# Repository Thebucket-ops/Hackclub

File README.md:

# BUCKPAD

hackpad for hackclub blueprint
The buckpad is a 11 key macropad with a rotary encoder and a OLED display, and uses QMK firmware.
The case is designed around the colors of gyspy danger from Pacific Rim, as it is one of the greatest films ever with NO sequel.
It mainly serves as a macropad for everyday activity (listening to music, writing etc.)

Features:
-11 keys
-1 EC11 rotary encoder
-1 Oled display

## PCB
here is the PCB (first time ever i do one!), the silkscreen is imported from a Figma image.

PCB design (I added a filling so its a bit messy, yikes)

Schematic for the hackpad

## Case Design
This was my first time working with Fusion and, not gonna lie, i had a ton of fun designing this case

## Firmware
This hackapd uses QMK firmware:
* the rotary encoder changes volume. press to mute
* the other 11 keys currently act as macros (thought i plan on implementing VIA to dynamically change them)
* I plan to set the oled as an audio visualizer once i get my hands on it.

## BOM

* 1x unsoldered Seeed XIAO RP2040
* 1x 0.91 inch OLED display
* 12x through-hole 1N4148 Diodes
* 11 MX-Style switches
* 1x EC11 Rotary encoder
* 11x white blank DSA keycaps
* 4x M3x16mm screws
* 4x M3x5mx4mm heatset inserts
* 1x Case (2 printed parts)

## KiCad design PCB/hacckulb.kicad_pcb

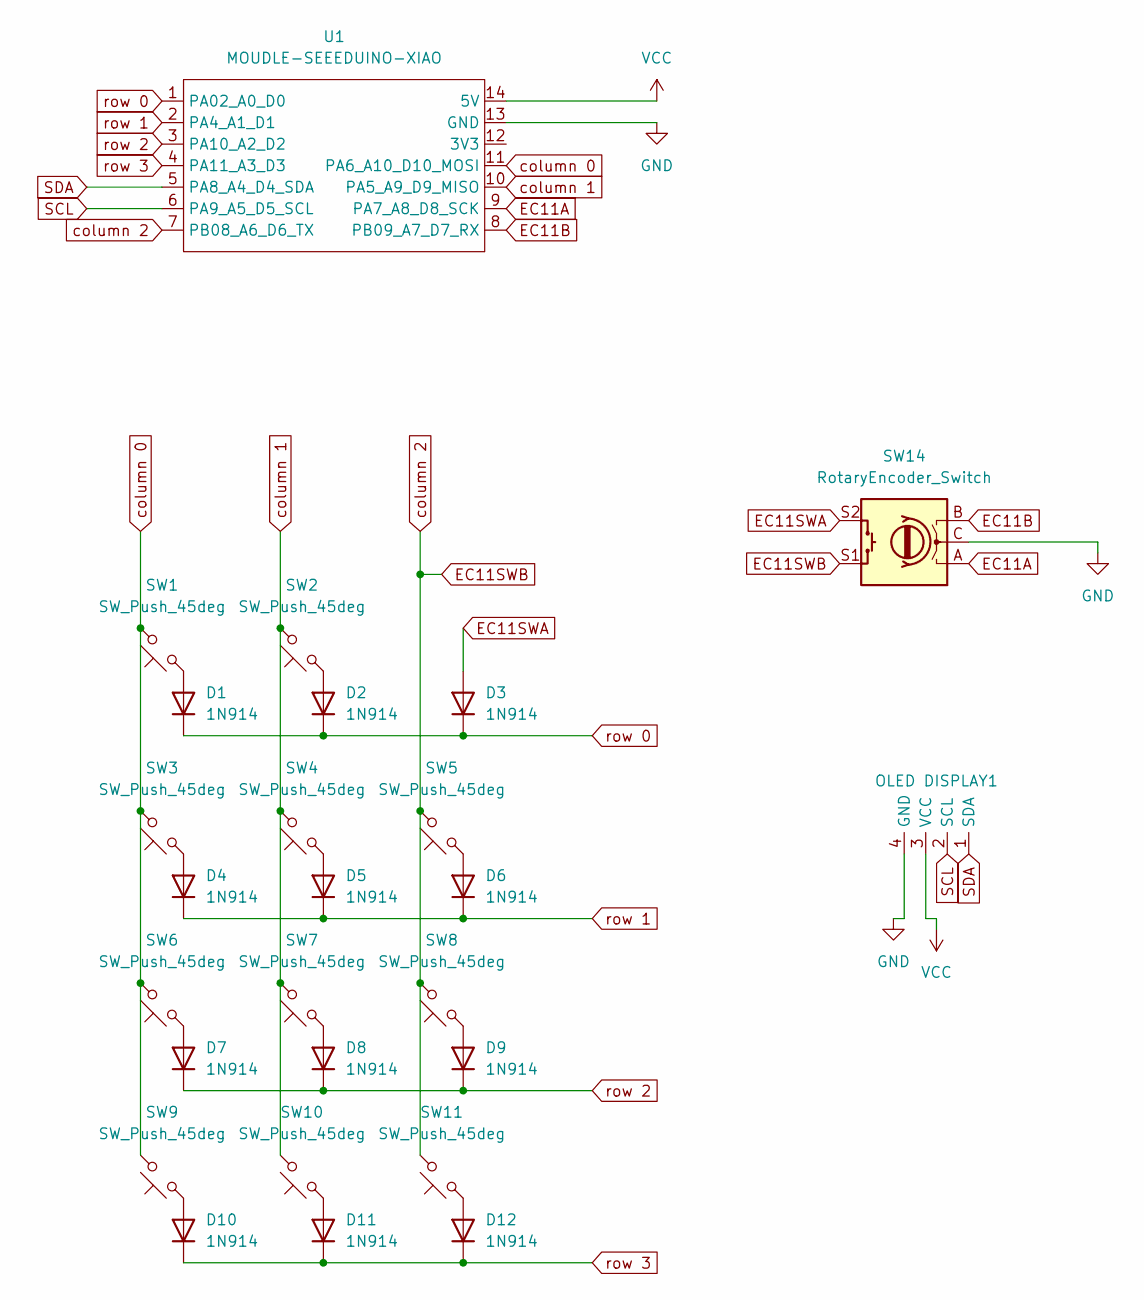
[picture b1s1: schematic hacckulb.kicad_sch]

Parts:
D1, D2, D3, D4, D5, D6, D7, D8, D9, D10, D11, D12: 1N914; D_DO-35_SOD27_P7.62mm_Horizontal
OLED DISPLAY1: SSD1306-0.91-OLED-4pin-128x32
SW1, SW2, SW3, SW4, SW5, SW6, SW7, SW8, SW9, SW10, SW11: SW_Push_45deg; SW_Cherry_MX_1.00u_PCB
SW14: RotaryEncoder_Switch; RotaryEncoder_Alps_EC11E-Switch_Vertical_H20mm
U1: MOUDLE-SEEEDUINO-XIAO; XIAO-Generic-Hybrid-14P-2.54-21X17.8MM

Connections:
EC11A: SW14.A, U1.9 (PA7_A8_D8_SCK)
EC11B: SW14.B, U1.8 (PB09_A7_D7_RX)
EC11SWA: D3.2 (A), SW14.S2
EC11SWB: SW5.2, SW8.2, SW11.2, SW14.S1, U1.7 (PB08_A6_D6_TX)
GND: OLED DISPLAY1.4 (GND), SW14.C, U1.13 (GND)
unnamed: D1.2 (A), SW1.1
unnamed: D2.2 (A), SW2.1
unnamed: D4.2 (A), SW3.1
unnamed: D5.2 (A), SW4.1
unnamed: D6.2 (A), SW5.1
unnamed: D7.2 (A), SW6.1
unnamed: D8.2 (A), SW7.1
unnamed: D9.2 (A), SW8.1
unnamed: D10.2 (A), SW9.1
unnamed: D11.2 (A), SW10.1
unnamed: D12.2 (A), SW11.1
SCL: OLED DISPLAY1.2 (SCL), U1.6 (PA9_A5_D5_SCL)
SDA: OLED DISPLAY1.1 (SDA), U1.5 (PA8_A4_D4_SDA)
VCC: OLED DISPLAY1.3 (VCC), U1.14 (5V)
column 0: SW1.2, SW3.2, SW6.2, SW9.2, U1.11 (PA6_A10_D10_MOSI)
column 1: SW2.2, SW4.2, SW7.2, SW10.2, U1.10 (PA5_A9_D9_MISO)
row 0: D1.1 (K), D2.1 (K), D3.1 (K), U1.1 (PA02_A0_D0)
row 1: D4.1 (K), D5.1 (K), D6.1 (K), U1.2 (PA4_A1_D1)
row 2: D7.1 (K), D8.1 (K), D9.1 (K), U1.3 (PA10_A2_D2)
row 3: D10.1 (K), D11.1 (K), D12.1 (K), U1.4 (PA11_A3_D3)

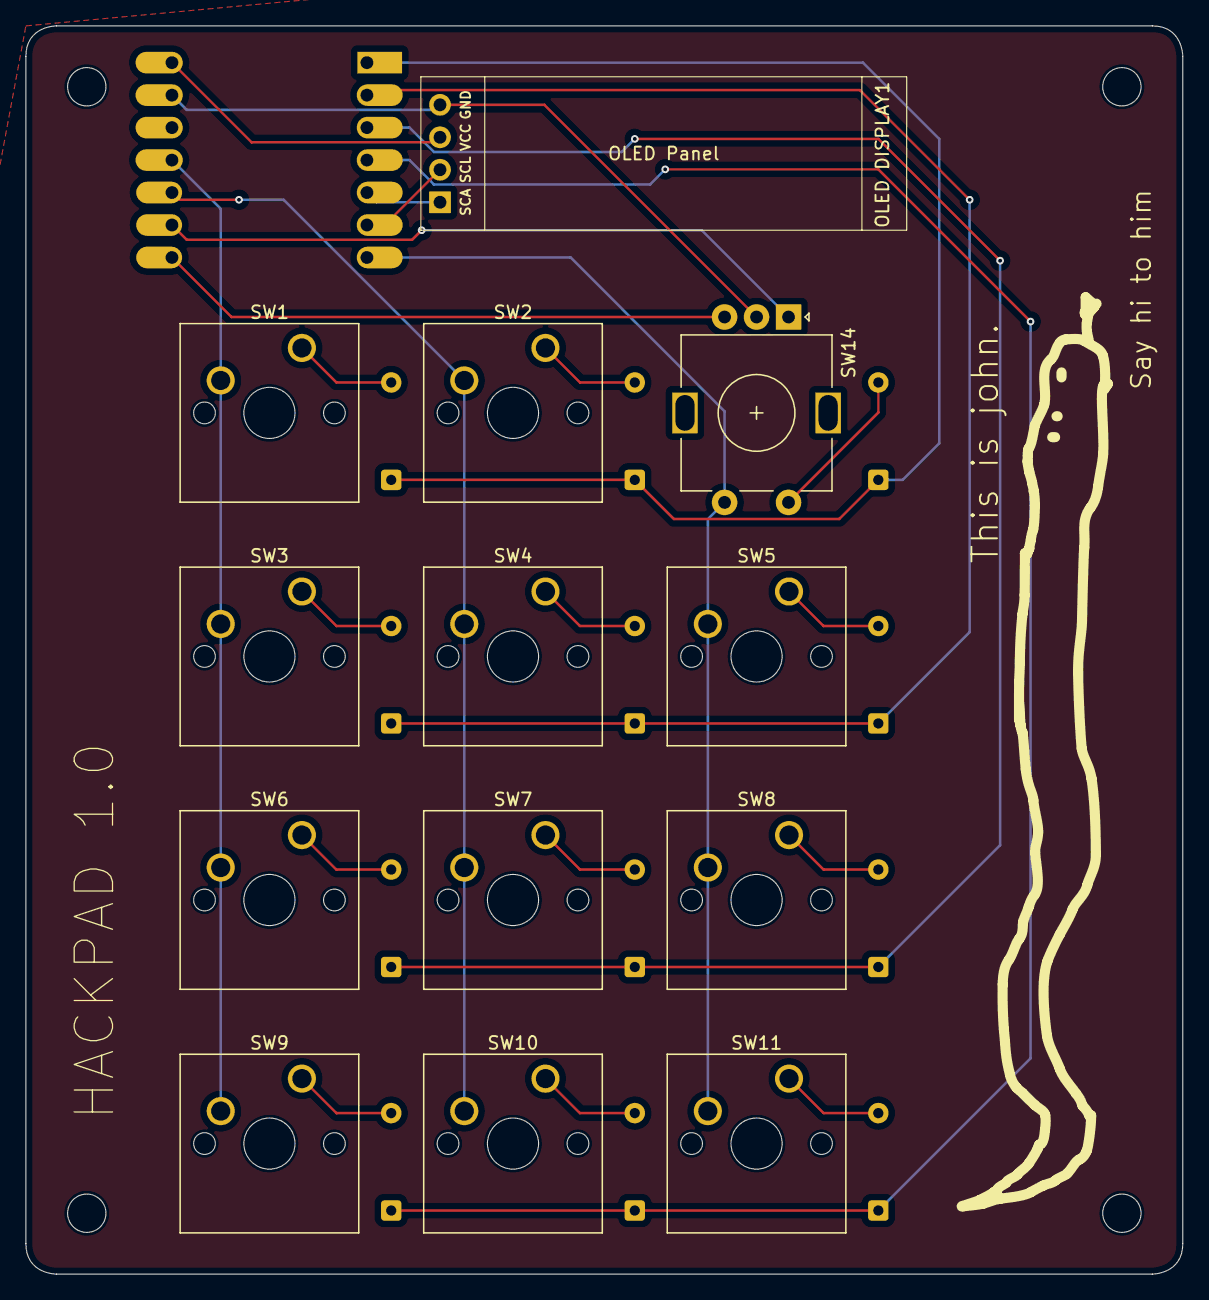
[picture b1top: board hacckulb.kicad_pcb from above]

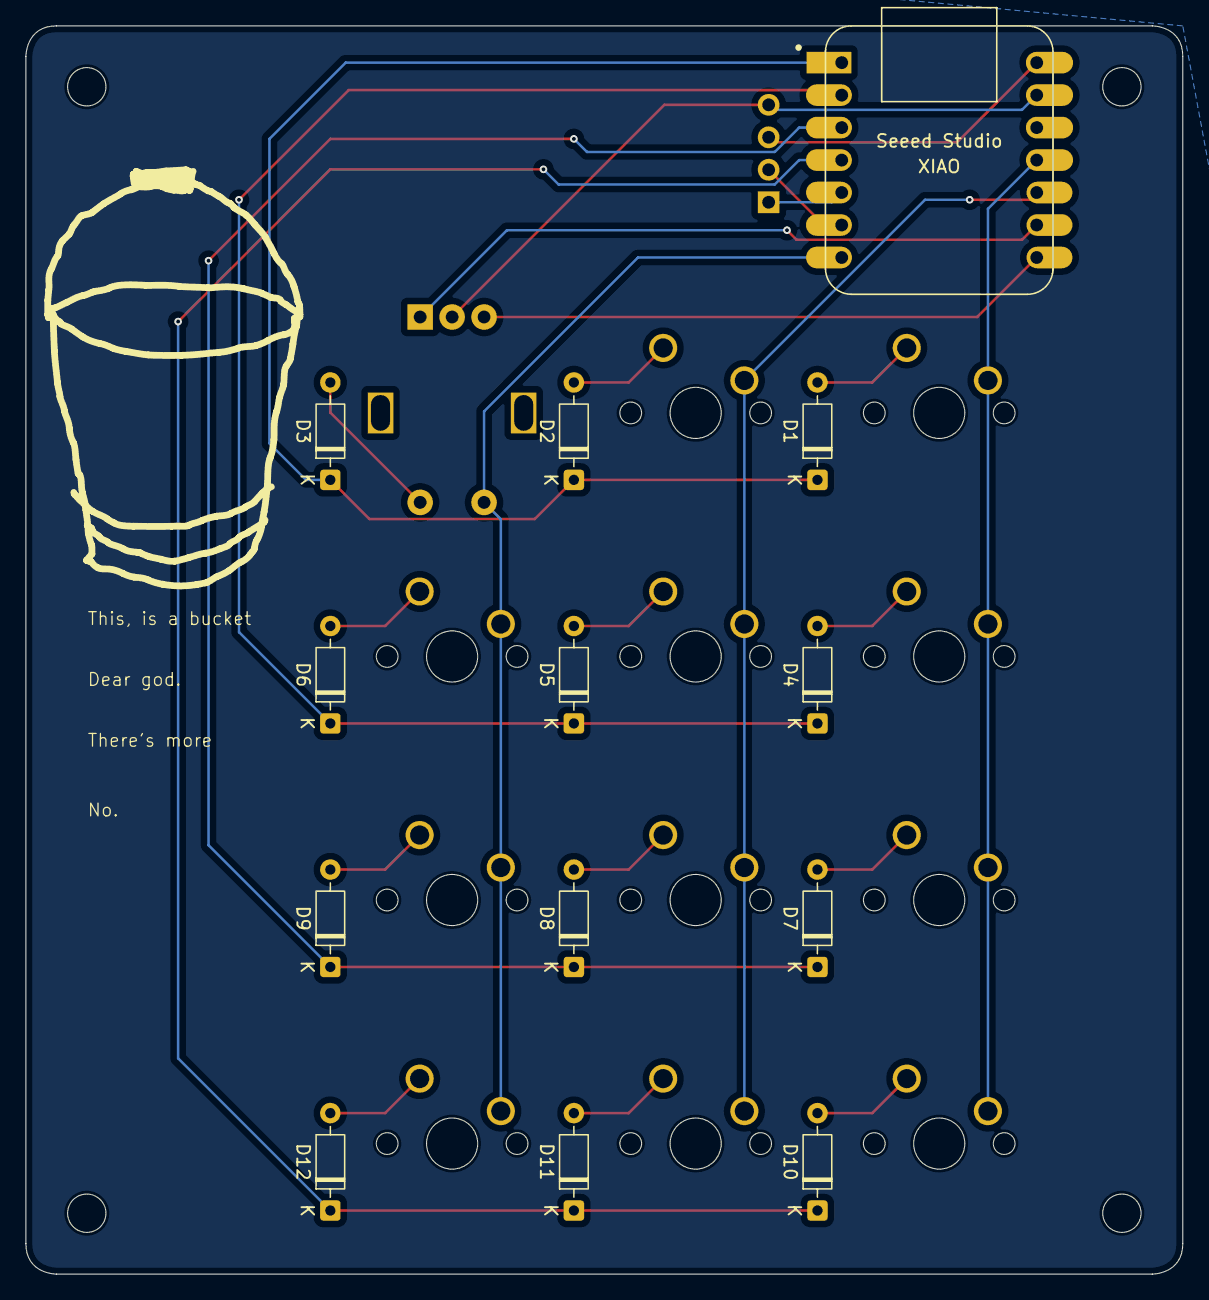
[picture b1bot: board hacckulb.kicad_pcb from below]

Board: 2 copper layers, 90.5 x 97.6 mm, 26 parts (13 on the bottom side), 25 nets.

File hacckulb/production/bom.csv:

Designator,Footprint,Quantity,Value,LCSC Part #
"D1, D10, D11, D12, D2, D3, D4, D5, D6, D7, D8, D9",D_DO-35_SOD27_P7.62mm_Horizontal,12,1N914,
OLED DISPLAY1,SSD1306-0.91-OLED-4pin-128x32,1,~,
"SW1, SW10, SW11, SW2, SW3, SW4, SW5, SW6, SW7, SW8, SW9",SW_Cherry_MX_1.00u_PCB,11,SW_Push_45deg,
SW14,RotaryEncoder_Alps_EC11E-Switch_Vertical_H20mm,1,RotaryEncoder_Switch,
U1,XIAO-Generic-Hybrid-14P-2.54-21X17.8MM,1,MOUDLE-SEEEDUINO-XIAO,

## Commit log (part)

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2026-03-23 -updated pcb to contain 3d models
2026-03-23 -reorganized location of pcb files and added firmware (a bit rudimental, but it should work)
2026-03-23 -added CAD folder and 3d models of the build inside of it
2026-03-23 reordered things, added cads and added readme
2026-03-23 corrected some mistakes
2026-04-04 updated firmware and fixed pcb (which i printed wrong :( ))
2026-06-12 Create LICENSE
